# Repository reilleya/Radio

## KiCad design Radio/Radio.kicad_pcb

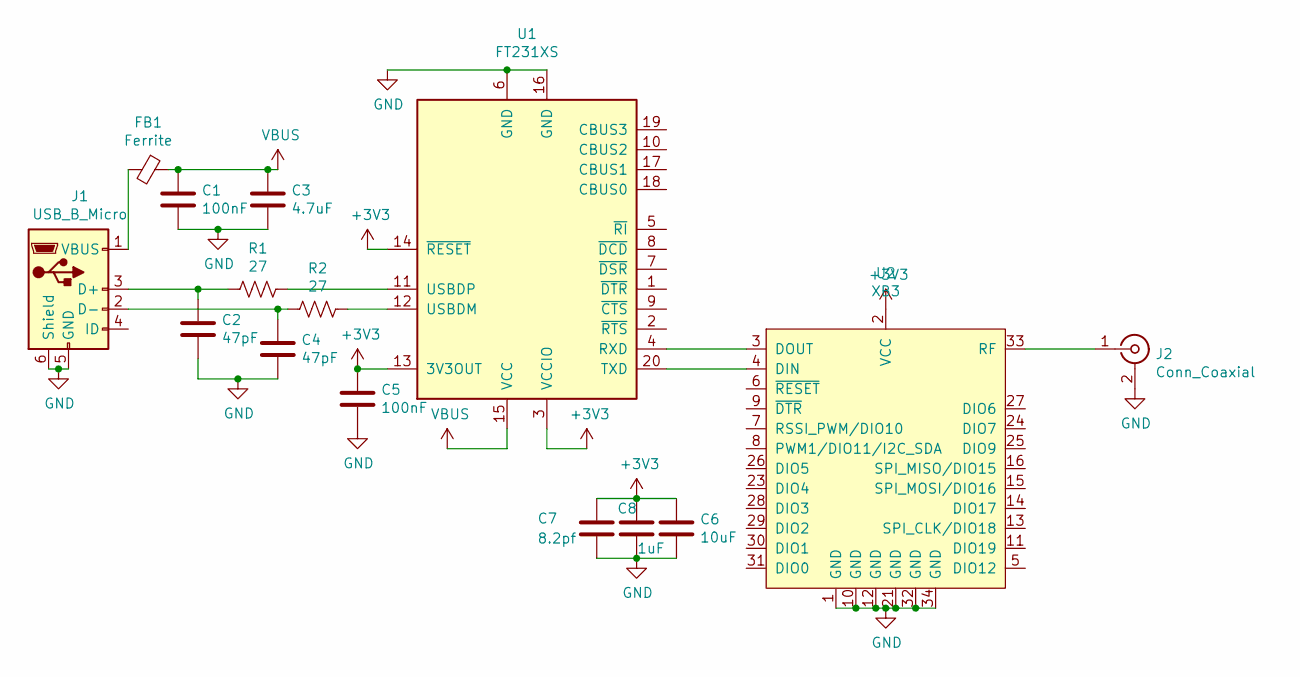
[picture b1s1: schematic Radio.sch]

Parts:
C1, C5: 100nF; C_0805_2012Metric_Pad1.15x1.40mm_HandSolder
C2, C4: 47pF; C_0805_2012Metric_Pad1.15x1.40mm_HandSolder
C3: 4.7uF; C_0805_2012Metric_Pad1.15x1.40mm_HandSolder
C6: 10uF; C_0805_2012Metric_Pad1.15x1.40mm_HandSolder
C7: 8.2pf; C_0805_2012Metric_Pad1.15x1.40mm_HandSolder
C8: 1uF; C_0805_2012Metric_Pad1.15x1.40mm_HandSolder
FB1: Ferrite; C_0805_2012Metric_Pad1.15x1.40mm_HandSolder
J1: USB_B_Micro; USB_Mini-B_Lumberg_2486_01_Horizontal
J2: Conn_Coaxial; SMA_Samtec_SMA-J-P-H-ST-EM1_EdgeMount
R1, R2: 27; R_0805_2012Metric_Pad1.15x1.40mm_HandSolder
U1: FT231XS; SSOP-20_3.9x8.7mm_P0.635mm
U2: XB3; XB3-24Z8RM-J

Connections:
+3V3: C5.1, C6.1, C7.1, C8.1, U1.3 (VCCIO), U1.13 (3V3OUT), U1.14 (~RESET), U2.2 (VCC)
GND: C1.2, C2.2, C3.2, C4.2, C5.2, C6.2, C7.2, C8.2, J1.5 (GND), J1.6 (Shield), J2.2 (Ext), U1.6 (GND), U1.16 (GND), U2.1 (GND), U2.10 (GND), U2.12 (GND), U2.21 (GND), U2.32 (GND), U2.34 (GND)
unnamed: C2.1, J1.3 (D+), R1.2
unnamed: C4.1, J1.2 (D-), R2.2
unnamed: FB1.2, J1.1 (VBUS)
unnamed: J2.1 (In), U2.33 (RF)
unnamed: R1.1, U1.11 (USBDP)
unnamed: R2.1, U1.12 (USBDM)
unnamed: U1.4 (RXD), U2.3 (DOUT)
unnamed: U1.20 (TXD), U2.4 (DIN)
VBUS: C1.1, C3.1, FB1.1, U1.15 (VCC)

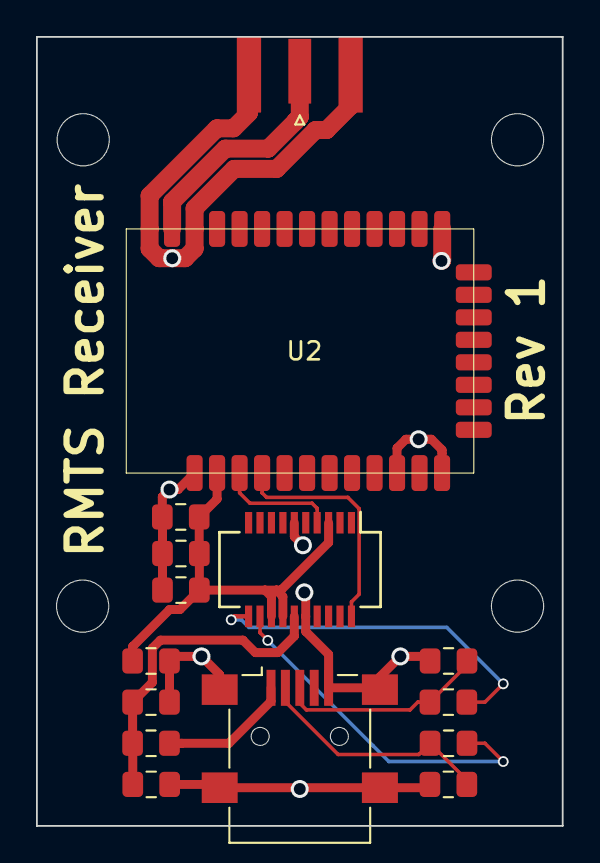
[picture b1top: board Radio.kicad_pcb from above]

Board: 2 copper layers, 29.2 x 43.8 mm, 15 parts (0 on the bottom side), 11 nets.

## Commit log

2019-12-29 Completed schematic
2019-12-29 Added proper xbee footprint, did initial layout
2019-12-30 Revised layout significantly
2020-01-02 Fixed RF trace impedance
2020-01-07 Shrank RP-SMA footprint
2020-04-26 Add silkscreen rectangle for SN, reduce mounting hole size
2020-06-30 Add LCSC part numbers
